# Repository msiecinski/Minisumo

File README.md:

# Minisumo
Source file, pcb and stl files.

## Design assumptions:
- 4 wheels
- STM32H753VIT6 MCU
- used start module
- 10 x 10 cm
- 500 g
- 4 x pololu HPCB 15:1 6V motor
- 4 x encoders(1 for each wheel)
- 6 x sharp sensor(GP2Y0D340K)
- 3 x ktir sensor

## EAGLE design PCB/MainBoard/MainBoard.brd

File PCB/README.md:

# List of PCBs
- sharp board
- main board

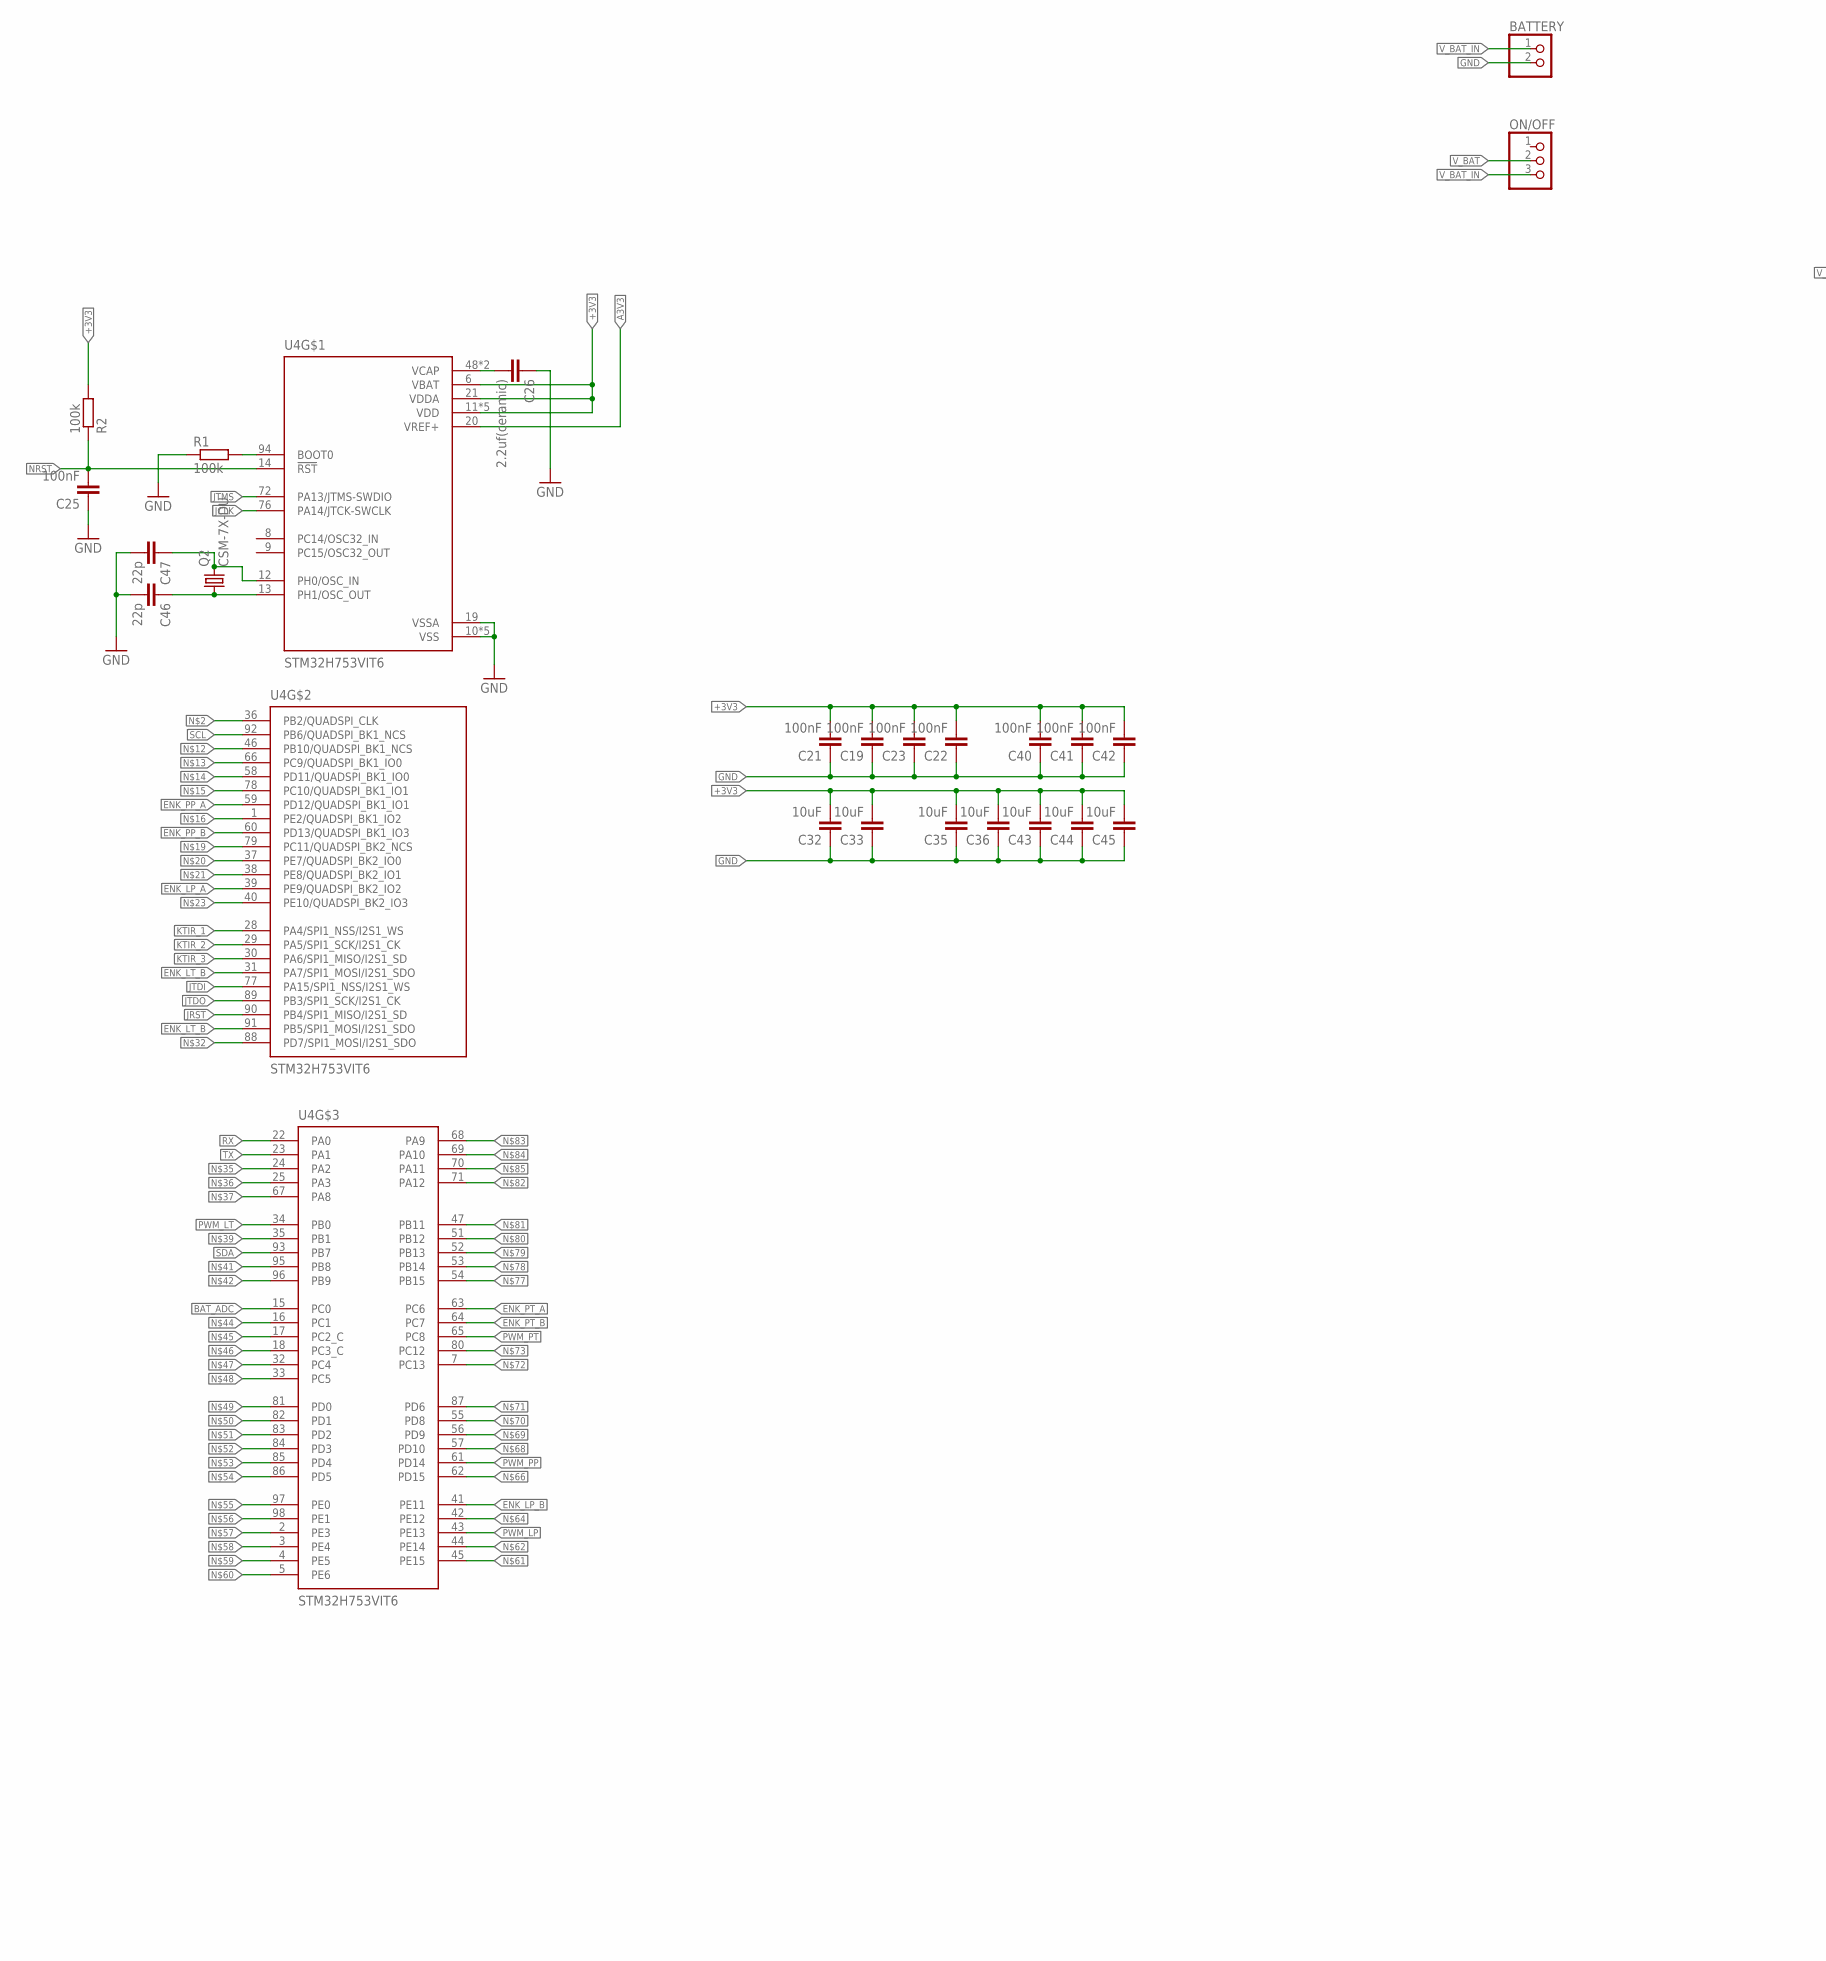
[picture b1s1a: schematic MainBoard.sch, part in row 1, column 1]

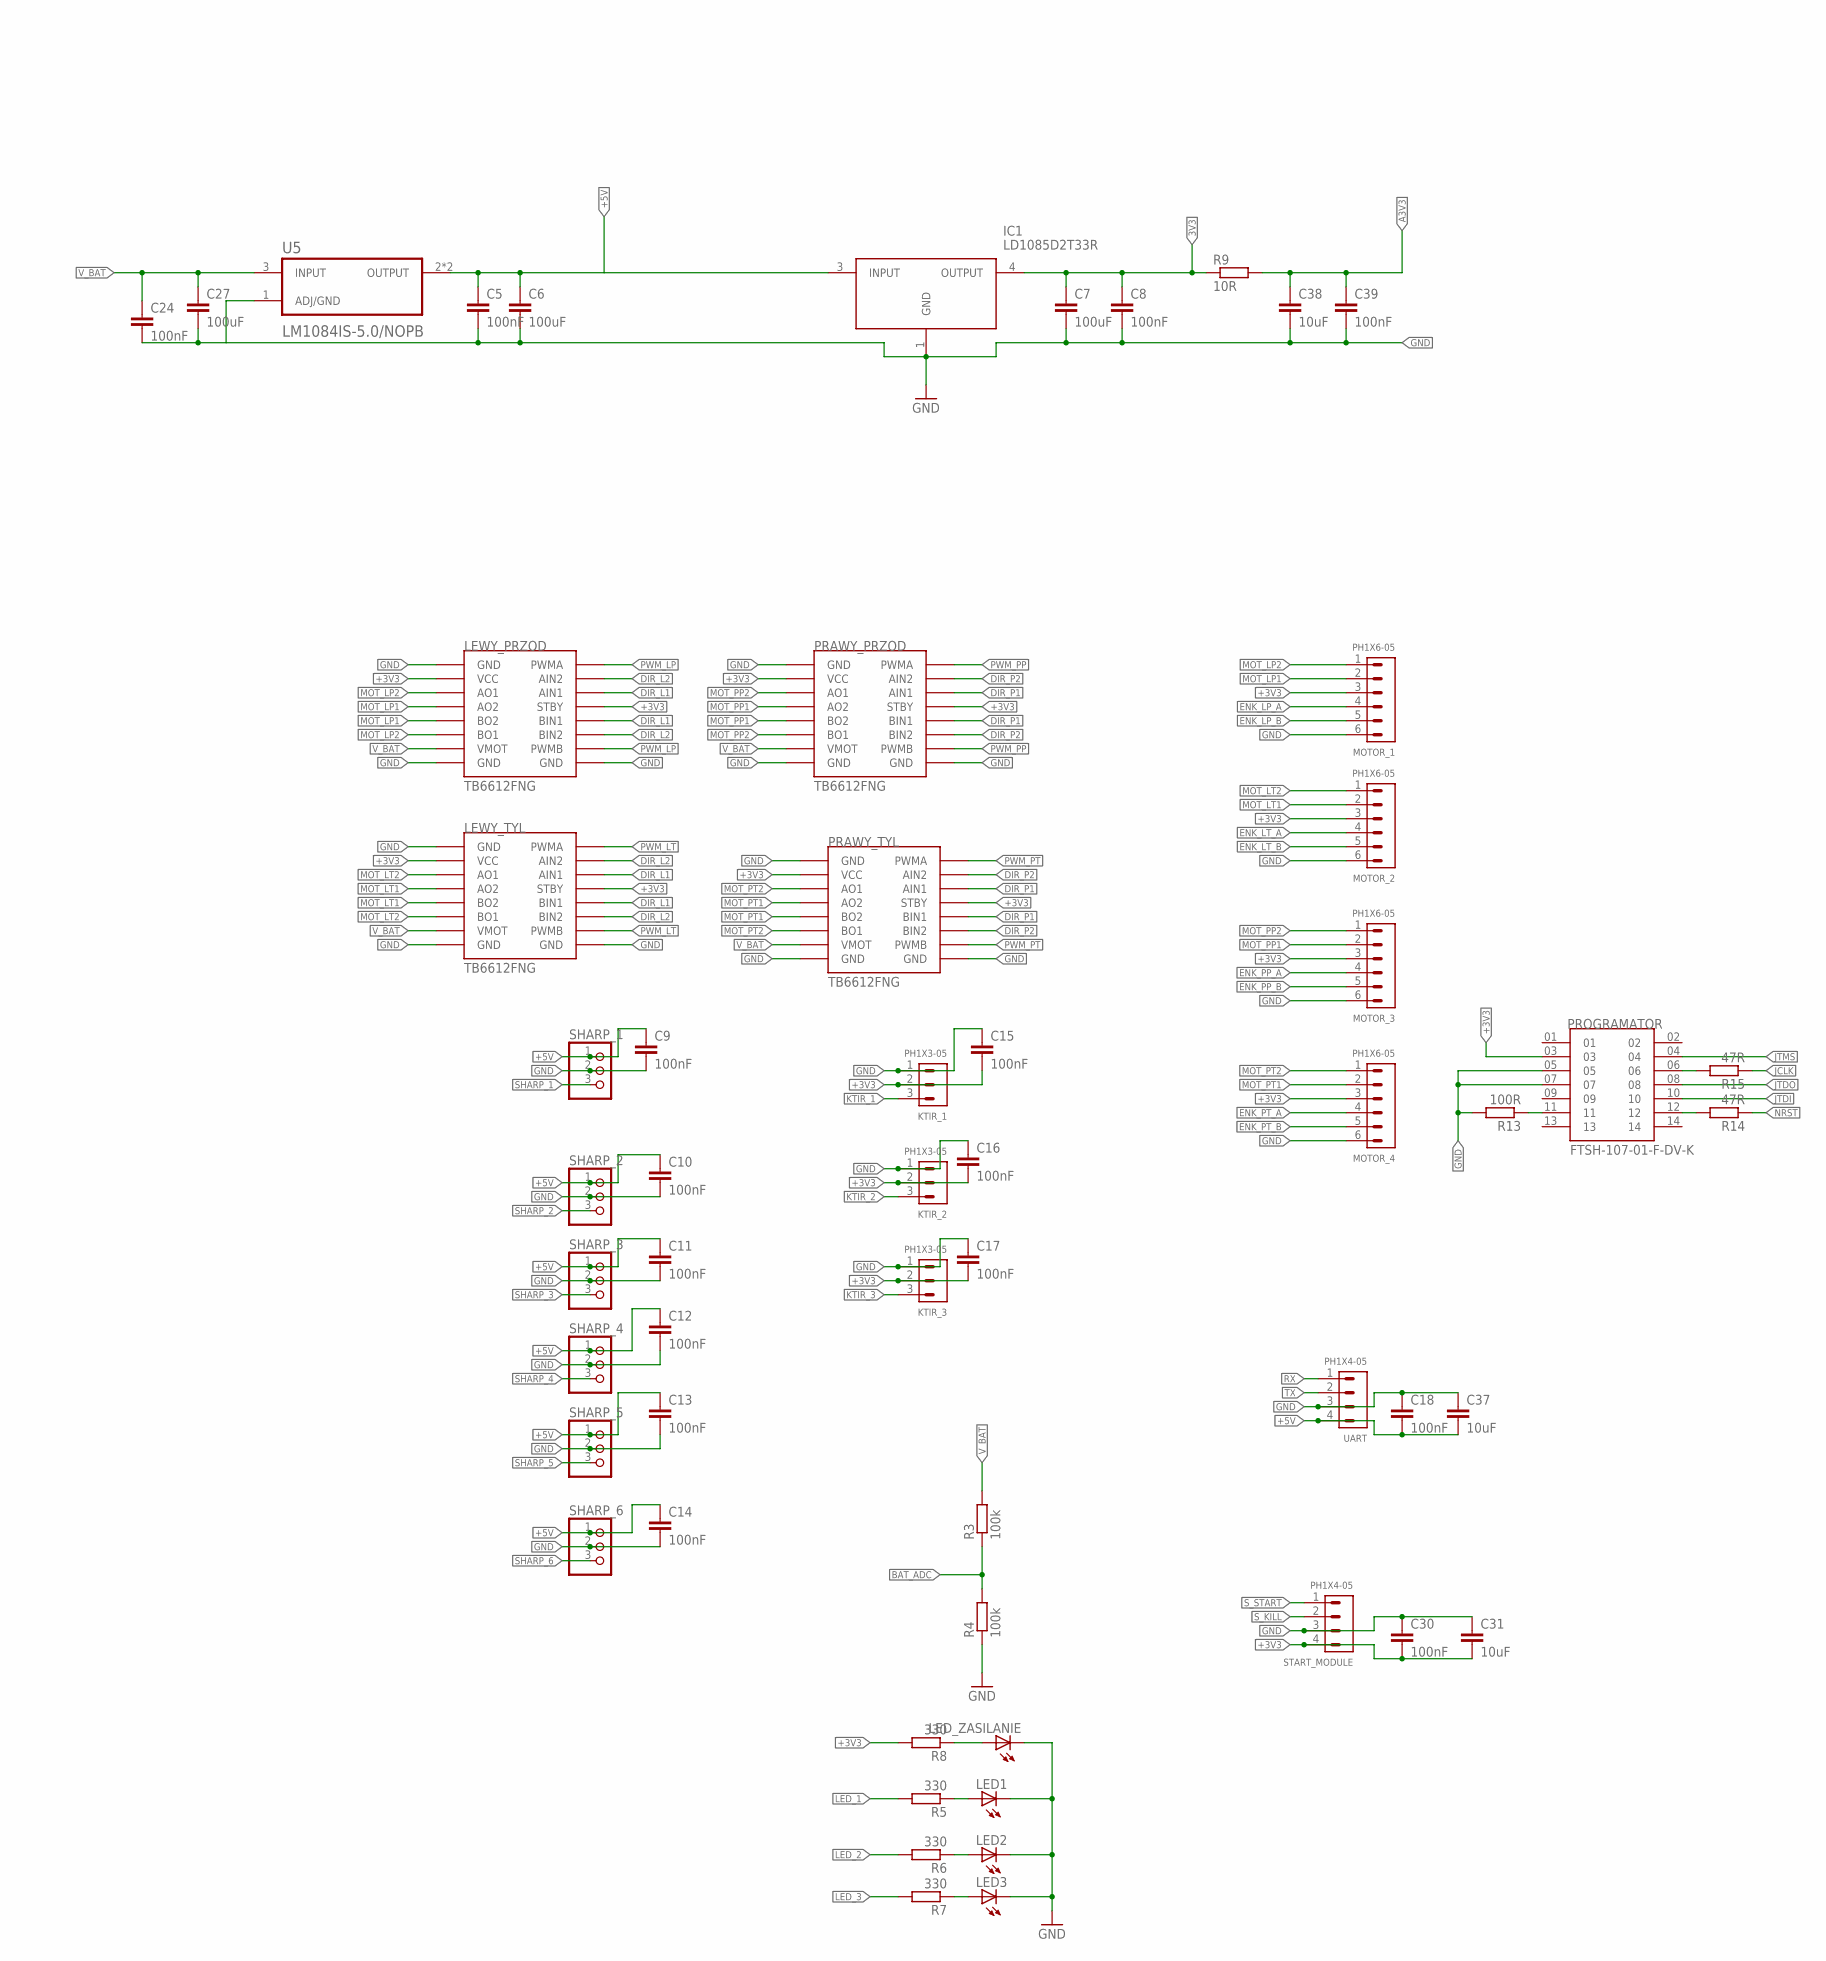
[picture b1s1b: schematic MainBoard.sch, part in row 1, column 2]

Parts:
BATTERY: PINHD-1X2; 1X02
C5, C8, C9, C10, C11, C12, C13, C14, C15, C16, C17, C18, C19, C21, C22, C23, C24, C25, C30, C39, C40, C41, C42: 100nF; C0805
C6, C7, C27: 100uF; C0805
C26: 2.2uf(ceramic); C0805
C31, C32, C33, C35, C36, C37, C38, C43, C44, C45: 10uF; C0805
C46, C47: 22p; C0805
IC1: LD1085D2T33R
KTIR_1, KTIR_2, KTIR_3: PH1X3-05; PH005-1-3
LED1, LED2, LED3: LEDCHIPLED_0805; CHIPLED_0805
LED_ZASILANIE: LEDCHIPLED_0805; CHIPLED_0805
LEWY_PRZOD: MODUL_POLOLU
LEWY_TYL: MODUL_POLOLU
MOTOR_1, MOTOR_2, MOTOR_3, MOTOR_4: PH1X6-05; PH005-1-6
ON/OFF: PINHD-1X3; 1X03
PRAWY_PRZOD: MODUL_POLOLU
PRAWY_TYL: MODUL_POLOLU
PROGRAMATOR: FTSH-107-01-F-DV-K; SAMTEC_FTSH-107-01-F-DV-K
Q2: CSM-7X-DU
R1, R2, R3, R4: 100k; M0805
R5, R6, R7, R8: 330; M0805
R9: 10R; M0805
R13: 100R; M0805
R14, R15: 47R; M0805
SHARP_1, SHARP_2, SHARP_3, SHARP_4, SHARP_5, SHARP_6: PINHD-1X3; 1X03
START_MODULE: PH1X4-05; PH005-1-4
U4: STM32H753VIT6; QFP50P1600X1600X160-100N
U5: LM1084IS-5.0/NOPB; TO254P1524X483-4N
UART: PH1X4-05; PH005-1-4

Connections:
3V3: C7.1, C8.1, IC1.4 (OUTPUT), R9.1
+3V3: C15.2, C16.2, C17.2, C19.2, C21.2, C22.2, C23.2, C30.2, C31.2, C32.2, C33.2, C35.2, C36.2, C40.2, C41.2, C42.2, C43.2, C44.2, C45.2, KTIR_1.2, KTIR_2.2, KTIR_3.2, LEWY_PRZOD.STBY, LEWY_PRZOD.VCC, LEWY_TYL.STBY, LEWY_TYL.VCC, MOTOR_1.3, MOTOR_2.3, MOTOR_3.3, MOTOR_4.3, PRAWY_PRZOD.STBY, PRAWY_PRZOD.VCC, PRAWY_TYL.STBY, PRAWY_TYL.VCC, PROGRAMATOR.03, R2.2, R8.2, START_MODULE.4, U4.6 (VBAT), U4.11 (VDD), U4.21 (VDDA), U4.27 (VDD), U4.50 (VDD), U4.75 (VDD), U4.100 (VDD)
+5V: C5.1, C6.1, C9.1, C10.1, C11.1, C12.1, C13.1, C14.1, C18.2, C37.2, IC1.3 (INPUT), SHARP_1.1, SHARP_2.1, SHARP_3.1, SHARP_4.1, SHARP_5.1, SHARP_6.1, U5.2 (OUTPUT), U5.4 (OUTPUT), UART.4
A3V3: C38.1, C39.1, R9.2, U4.20 (VREF+)
BAT_ADC: R3.1, R4.2, U4.15 (PC0)
DIR_L1: LEWY_PRZOD.AIN1, LEWY_PRZOD.BIN1, LEWY_TYL.AIN1, LEWY_TYL.BIN1
DIR_L2: LEWY_PRZOD.AIN2, LEWY_PRZOD.BIN2, LEWY_TYL.AIN2, LEWY_TYL.BIN2
DIR_P1: PRAWY_PRZOD.AIN1, PRAWY_PRZOD.BIN1, PRAWY_TYL.AIN1, PRAWY_TYL.BIN1
DIR_P2: PRAWY_PRZOD.AIN2, PRAWY_PRZOD.BIN2, PRAWY_TYL.AIN2, PRAWY_TYL.BIN2
ENK_LP_A: MOTOR_1.4, U4.39 (PE9/QUADSPI_BK2_IO2)
ENK_LP_B: MOTOR_1.5, U4.41 (PE11)
ENK_LT_A: MOTOR_2.4
ENK_LT_B: MOTOR_2.5, U4.31 (PA7/SPI1_MOSI/I2S1_SDO), U4.91 (PB5/SPI1_MOSI/I2S1_SDO)
ENK_PP_A: MOTOR_3.4, U4.59 (PD12/QUADSPI_BK1_IO1)
ENK_PP_B: MOTOR_3.5, U4.60 (PD13/QUADSPI_BK1_IO3)
ENK_PT_A: MOTOR_4.4, U4.63 (PC6)
ENK_PT_B: MOTOR_4.5, U4.64 (PC7)
GND: BATTERY.2, C5.2, C6.2, C7.2, C8.2, C9.2, C10.2, C11.2, C12.2, C13.2, C14.2, C15.1, C16.1, C17.1, C18.1, C19.1, C21.1, C22.1, C23.1, C25.1, C26.1, C30.1, C31.1, C32.1, C33.1, C35.1, C36.1, C37.1, C38.2, C39.2, C40.1, C41.1, C42.1, C43.1, C44.1, C45.1, C46.2, C47.2, IC1.1 (GND), KTIR_1.1, KTIR_2.1, KTIR_3.1, LED1.C, LED2.C, LED3.C, LED_ZASILANIE.C, LEWY_PRZOD.GND1 (GND), LEWY_PRZOD.GND2 (GND), LEWY_PRZOD.GND3 (GND), LEWY_TYL.GND1 (GND), LEWY_TYL.GND2 (GND), LEWY_TYL.GND3 (GND), MOTOR_1.6, MOTOR_2.6, MOTOR_3.6, MOTOR_4.6, PRAWY_PRZOD.GND1 (GND), PRAWY_PRZOD.GND2 (GND), PRAWY_PRZOD.GND3 (GND), PRAWY_TYL.GND1 (GND), PRAWY_TYL.GND2 (GND), PRAWY_TYL.GND3 (GND), PROGRAMATOR.05, PROGRAMATOR.07, R1.1, R4.1, R13.2, SHARP_1.2, SHARP_2.2, SHARP_3.2, SHARP_4.2, SHARP_5.2, SHARP_6.2, START_MODULE.3, U4.10 (VSS), U4.19 (VSSA), U4.26 (VSS), U4.49 (VSS), U4.74 (VSS), U4.99 (VSS), UART.3
JCLK: R15.1, U4.76 (PA14/JTCK-SWCLK)
JRST: U4.90 (PB4/SPI1_MISO/I2S1_SD)
JTDI: PROGRAMATOR.10, U4.77 (PA15/SPI1_NSS/I2S1_WS)
JTDO: PROGRAMATOR.08, U4.89 (PB3/SPI1_SCK/I2S1_CK)
JTMS: PROGRAMATOR.04, U4.72 (PA13/JTMS-SWDIO)
KTIR_1: KTIR_1.3, U4.28 (PA4/SPI1_NSS/I2S1_WS)
KTIR_2: KTIR_2.3, U4.29 (PA5/SPI1_SCK/I2S1_CK)
KTIR_3: KTIR_3.3, U4.30 (PA6/SPI1_MISO/I2S1_SD)
LED_1: R5.2
LED_2: R6.2
LED_3: R7.2
MOT_LP1: LEWY_PRZOD.A02 (AO2), LEWY_PRZOD.BO2, MOTOR_1.2
MOT_LP2: LEWY_PRZOD.AO1, LEWY_PRZOD.BO1, MOTOR_1.1
MOT_LT1: LEWY_TYL.A02 (AO2), LEWY_TYL.BO2, MOTOR_2.2
MOT_LT2: LEWY_TYL.AO1, LEWY_TYL.BO1, MOTOR_2.1
MOT_PP1: MOTOR_3.2, PRAWY_PRZOD.A02 (AO2), PRAWY_PRZOD.BO2
MOT_PP2: MOTOR_3.1, PRAWY_PRZOD.AO1, PRAWY_PRZOD.BO1
MOT_PT1: MOTOR_4.2, PRAWY_TYL.A02 (AO2), PRAWY_TYL.BO2
MOT_PT2: MOTOR_4.1, PRAWY_TYL.AO1, PRAWY_TYL.BO1
unnamed: PROGRAMATOR.11, R13.1
unnamed: R1.2, U4.94 (BOOT0)
unnamed: C26.2, U4.48 (VCAP), U4.73 (VCAP)
unnamed: LED1.A, R5.1
unnamed: LED2.A, R6.1
unnamed: LED3.A, R7.1
unnamed: PROGRAMATOR.12, R14.2
unnamed: LED_ZASILANIE.A, R8.1
unnamed: C47.1, Q2.2, U4.12 (PH0/OSC_IN)
unnamed: C46.1, Q2.1, U4.13 (PH1/OSC_OUT)
unnamed: PROGRAMATOR.06, R15.2
unnamed: C24.2, C27.2, U5.1 (ADJ/GND)
NRST: C25.2, R2.1, R14.1, U4.14 (!RST)
PWM_LP: LEWY_PRZOD.PWMA, LEWY_PRZOD.PWMB, U4.43 (PE13)
PWM_LT: LEWY_TYL.PWMA, LEWY_TYL.PWMB, U4.34 (PB0)
PWM_PP: PRAWY_PRZOD.PWMA, PRAWY_PRZOD.PWMB, U4.61 (PD14)
PWM_PT: PRAWY_TYL.PWMA, PRAWY_TYL.PWMB, U4.65 (PC8)
RX: U4.22 (PA0), UART.1
SCL: U4.92 (PB6/QUADSPI_BK1_NCS)
SDA: U4.93 (PB7)
SHARP_1: SHARP_1.3
SHARP_2: SHARP_2.3
SHARP_3: SHARP_3.3
SHARP_4: SHARP_4.3
SHARP_5: SHARP_5.3
SHARP_6: SHARP_6.3
S_KILL: START_MODULE.2
S_START: START_MODULE.1
TX: U4.23 (PA1), UART.2
V_BAT: C24.1, C27.1, LEWY_PRZOD.VMOT, LEWY_TYL.VMOT, ON/OFF.2, PRAWY_PRZOD.VMOT, PRAWY_TYL.VMOT, R3.2, U5.3 (INPUT)
V_BAT_IN: BATTERY.1, ON/OFF.3

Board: 2 copper layers, 89 parts (11 on the bottom side), 53 nets, no tracks yet.

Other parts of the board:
U$1, U$2, U$3, U$4, U$5, U$6, U$7, U$8: 2,8

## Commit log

2021-10-08 Added cad files with v1 version robot chassis.
2021-10-08 Added readme file in mechanis folder.
2021-10-08 Added PCB with sharp sensor and readme file.
2021-10-09 Added second version of chassis.
2021-10-09 Added second version of chassis.
2021-10-09 Update holes size
2021-10-10 Some minior changes
2021-10-13 Increase space for sharp sensor
2021-10-13 Move (0.5mm) forvard motors
2021-10-15 Changes in chassis_v2 project -added mount hole for sharp sensor and upgrade place for sharp -delete part of holes for pcb -edit place for ktir and plow(less thickness 2.5->2mm) -shortened back of ch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
2021-10-17 Change place designed for plow
2021-10-17 Work on main board pcb
2022-03-08 Changing naming chassis V2(actual version)
2022-03-08 3d files update
    -increase hole for screw size
    -update place for sharps
    -narrowing by 6mm(3 on both size)
    -rear height increase
    -plew screw position change
2022-03-08 Update 3d files
    -increase length sharp srew hole
2022-03-10 Update readme
    - change selected MCU(STM32F4 instead of STM32H7)
    - added info about sharp sensor and ktir sensor
2022-03-10 Create README.md
    Added readme file
2022-03-10 Update 3d files
    -decrease srew hgole size for sharp
    -place for sharp on front
2022-03-16 Update cad files
    Update backside:
    -lining(3.5m->4.5mm)
    -place for hole(5mm->5.5mm)
2022-03-24 Update cad files
    -place for sharo sensor
    -move 2 holes for plow/pcb
2022-03-27 Added plow and submission
    -added plow v1
    -added submussion(plow + chassis)
2022-06-03 Update cad files
    Chassis:
    - remove place for sharo sensor
    -change posiotion 2 holes for mount plow(increase 9mm)
    Plow:
    -update postion hole for plow mount(increase by 9mm)
2022-06-03 Update README.md
    Change using in project MCU(STM32F466->STM32H7A3VIT6)
2022-06-03 Update README.md
    Fix error(STM32H753VIT6 no STM32H7A3VIT6)
2022-07-06 Main board updates
    -change mcu(STM32H753)
2022-07-06 Update eagle files
2022-07-12 PCB update
    -place elements on the board
2022-07-13 Update pcb files
    - edit positions on the board
2022-07-14 Update eagle files
    -delete gyroscope
